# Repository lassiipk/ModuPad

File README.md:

# MODUPAD
| CAD | *IRL* |
|-----------|-----|
|  |  |

**MODUPAD** is a compact **3×3 programmable macropad with a rotary encoder** designed with a **macro‑first, learning‑driven philosophy**.  

This project represents a **from‑scratch learning journey** covering electronics, schematic design, PCB layout, firmware architecture, and documentation—while still resulting in a practical, daily‑use device.

---
<!--
## Device Identity

> **MODUPAD** is a **3×3 macropad + rotary encoder** with layered keymaps, encoder‑driven system control, and an event‑based OLED interface.

---

## Project Goals

- Learn electronics **from near zero** through hands‑on design
- Design a complete keyboard matrix with diodes
- Integrate a microcontroller, rotary encoder, and OLED display
- Build a full PCB in KiCad (schematic → layout → DRC‑clean)
- Design firmware architecture before hardware arrival
- Practice clean documentation and GitHub‑based version control
- Produce a focused, usable macropad without feature creep

This project prioritizes **learning clarity, reasoning, and correctness** over visual complexity.
-->

<!--
## Final Key Features (As Built)

- **3×3 key matrix (9 keys)** dedicated entirely to macros
- **Multiple firmware layers**
  - Layer 0 (Default)
  - Layer 1 (Fn layer)
  - Layer 2 (planned / future)
- **EC11 rotary encoder**
  - Rotation: system volume control
  - Button: OLED mode control
- **0.91” 128×32 I²C OLED**
  - Animation mode
  - Text mode
  - Status mode
  - Full OFF state
- **USB‑C connectivity**
- **Windows‑focused macro design** (Windows 10 & 11)
- **No RGB lighting** (removed during redesign to reduce complexity)

---
<!--
## Encoder Behavior

### Encoder Rotation
- Controls **system volume only**
- Small step size for precision
- Works across **Windows 10 & 11**

### Encoder Button
- **Press:** Cycle OLED animations
- **Fn + Press:** Cycle text/status modes
- **Fn + Hold (3s):** OLED ON / OFF toggle

---

## OLED System

### OLED Modes
1. **Animation Mode**
   - Plays one full animation per `animation_xx.py`
   - Firmware auto‑detects all animation files
   - No hard limit on number of animations
2. **Text Mode**
   - Displays:
     - Creator name
     - Date & time
3. **Status Mode**
   - Displays system states (e.g. mute status)
4. **OFF Mode**
   - OLED fully powered down (true blank state)

OLED behavior is **event‑driven**, not continuously animated.

---

 ## Development Status (Current)

- [x] Concept defined
- [x] Schematic completed
- [x] PCB layout completed
- [x] DRC‑clean board
- [x] Case designed
- [x] Firmware architecture finalized
- [x] Firmware written
- [x] Project uploaded to GitHub
- [ ] Hardware fabrication & assembly
- [ ] Flashing & physical testing
-->

## Firmware Overview

- **Firmware Framework:** KMK (Python‑based)

---

<!-- **Reason for KMK**
  - Python readability
  - Clear firmware structure
  - No dependency on VIA
  - Easier reasoning without hardware in hand

Firmware was designed **before physical assembly**, allowing logic review and iteration in advance.

---

## Why MODUPAD?

**MODUPAD** stands for:
- **MODU** — Modular, adaptable, intentional
- **PAD** — A focused input device

Every decision made in this project supports **clarity, control, and learning**.

---

-->

## Bill of Materials (BOM):
- **Microcontroller:** Seeed Studio XIAO RP2040
- **Keys:** 9 × MX‑style switches
- **Diodes:** 10 1N4148 Diodes (matrix isolation)
- **Encoder:** EC11 rotary encoder with push button
- **Display:** 0.91” I²C OLED (128×32)
- **Connectivity:** USB‑C
- **Case:** Custom‑designed in Fusion 360, 3D‑printed

---

| Schematic | PCB | Case |
|-----------|-----|------|
|  |  |  |

---

### Timeline

**Project Started:** 19th December, 2025 | 11:58 PM

**Project Ended:** 2nd January, 2026 | 7:58 PM

**Project Submited:** 2nd January, 2026 | 11:17 PM

**Project 99% Completed:** 12 Febuary | 1:00 PM

**Project 100% Completed:** N/a

---

## License

This project is open‑source and intended for **educational and personal use**.

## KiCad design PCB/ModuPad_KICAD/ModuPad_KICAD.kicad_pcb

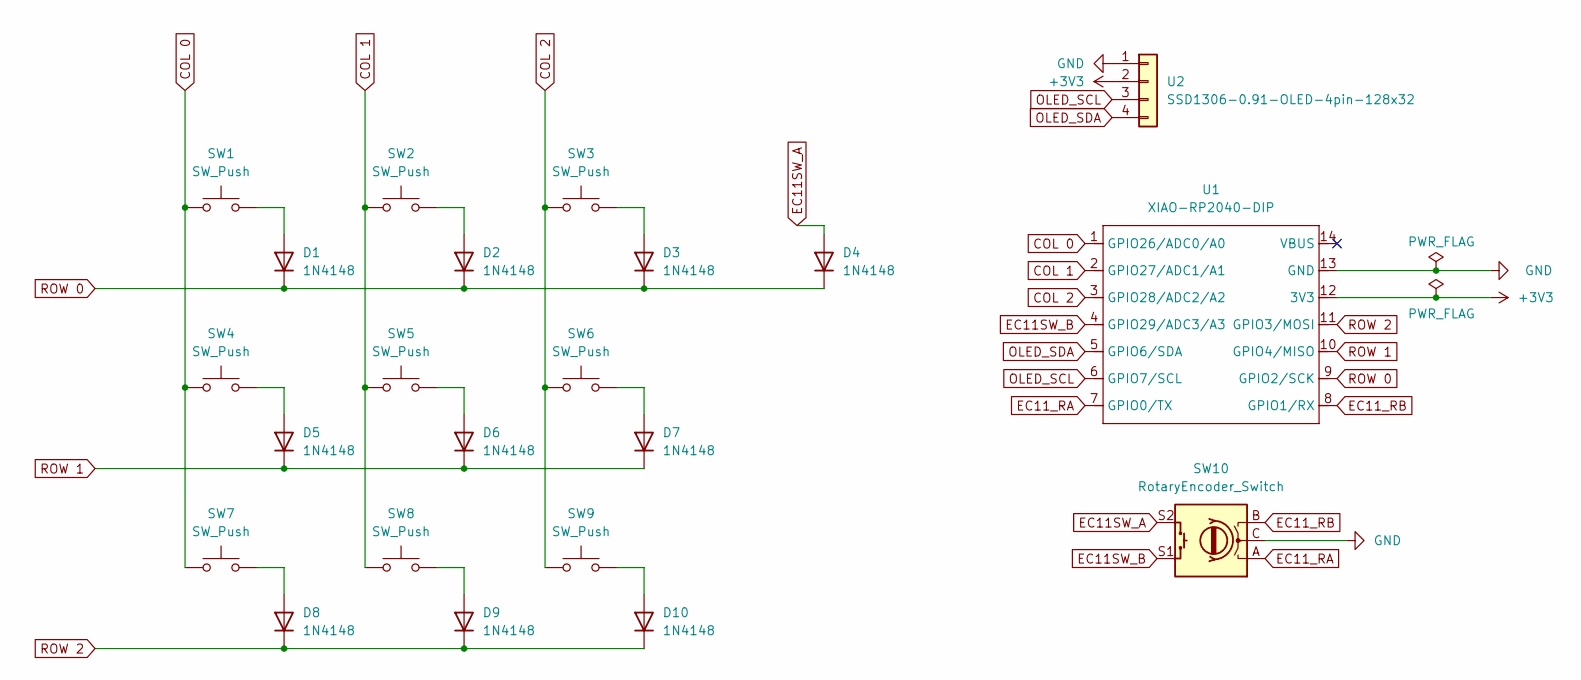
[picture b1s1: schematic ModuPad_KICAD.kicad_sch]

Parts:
D1, D2, D3, D4, D5, D6, D7, D8, D9, D10: 1N4148; D_DO-35_SOD27_P7.62mm_Horizontal
SW1, SW2, SW3, SW4, SW5, SW6, SW7, SW8, SW9: SW_Push; SW_Cherry_MX_1.00u_PCB
SW10: RotaryEncoder_Switch; RotaryEncoder_Alps_EC11E-Switch_Vertical_H20mm_CircularMoun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
U1: XIAO-RP2040-DIP
U2: SSD1306-0.91-OLED-4pin-128x32

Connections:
+3V3: U1.12 (3V3), U2.2
COL 0: SW1.1, SW4.1, SW7.1, U1.1 (GPIO26/ADC0/A0)
COL 1: SW2.1, SW5.1, SW8.1, U1.2 (GPIO27/ADC1/A1)
COL 2: SW3.1, SW6.1, SW9.1, U1.3 (GPIO28/ADC2/A2)
EC11SW_A: D4.2 (A), SW10.S2
EC11SW_B: SW10.S1, U1.4 (GPIO29/ADC3/A3)
EC11_RA: SW10.A, U1.7 (GPIO0/TX)
EC11_RB: SW10.B, U1.8 (GPIO1/RX)
GND: SW10.C, U1.13 (GND), U2.1
unnamed: D1.2 (A), SW1.2
unnamed: D2.2 (A), SW2.2
unnamed: D3.2 (A), SW3.2
unnamed: D5.2 (A), SW4.2
unnamed: D6.2 (A), SW5.2
unnamed: D7.2 (A), SW6.2
unnamed: D8.2 (A), SW7.2
unnamed: D9.2 (A), SW8.2
unnamed: D10.2 (A), SW9.2
OLED_SCL: U1.6 (GPIO7/SCL), U2.3
OLED_SDA: U1.5 (GPIO6/SDA), U2.4
ROW 0: D1.1 (K), D2.1 (K), D3.1 (K), D4.1 (K), U1.9 (GPIO2/SCK)
ROW 1: D5.1 (K), D6.1 (K), D7.1 (K), U1.10 (GPIO4/MISO)
ROW 2: D8.1 (K), D9.1 (K), D10.1 (K), U1.11 (GPIO3/MOSI)

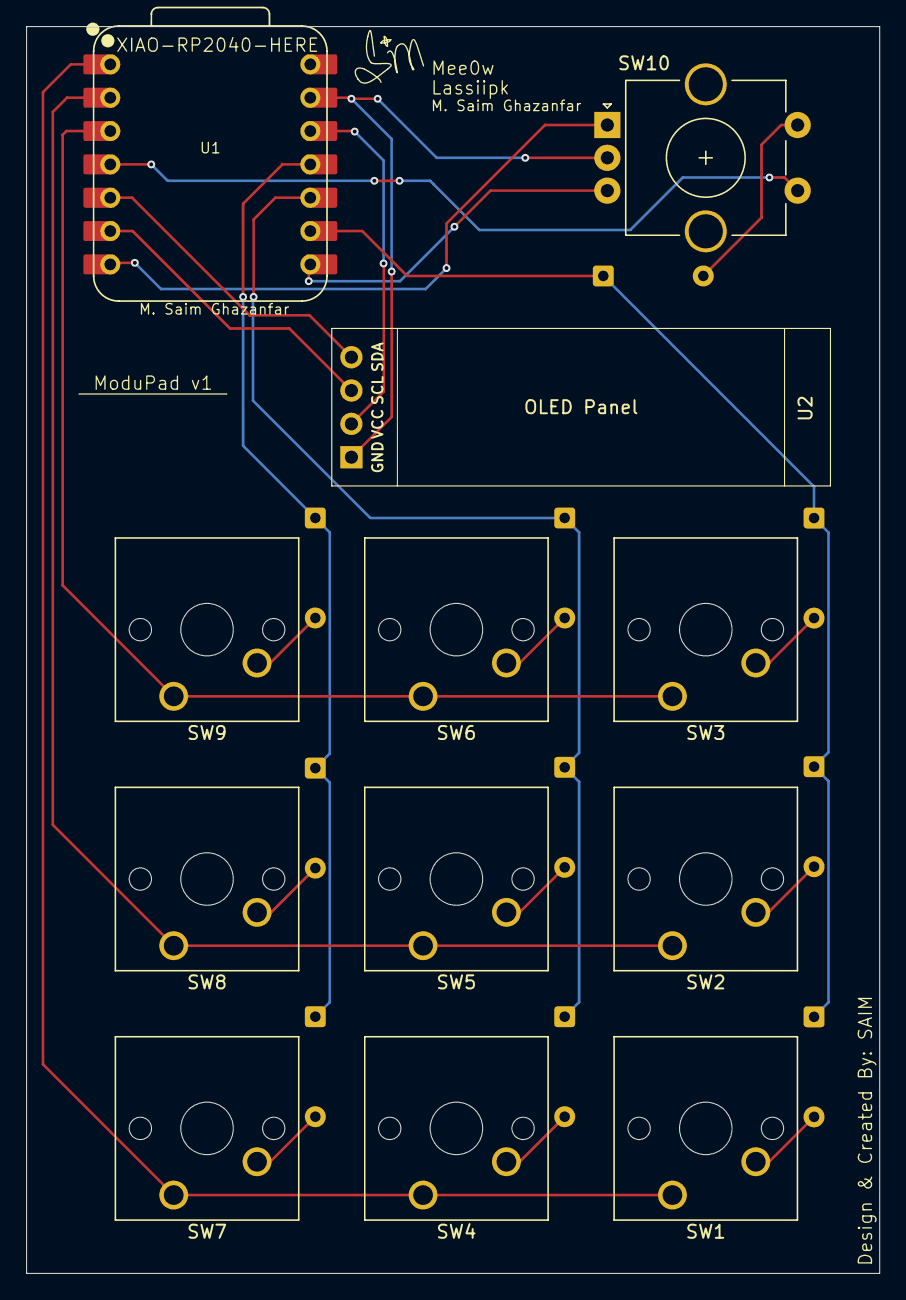
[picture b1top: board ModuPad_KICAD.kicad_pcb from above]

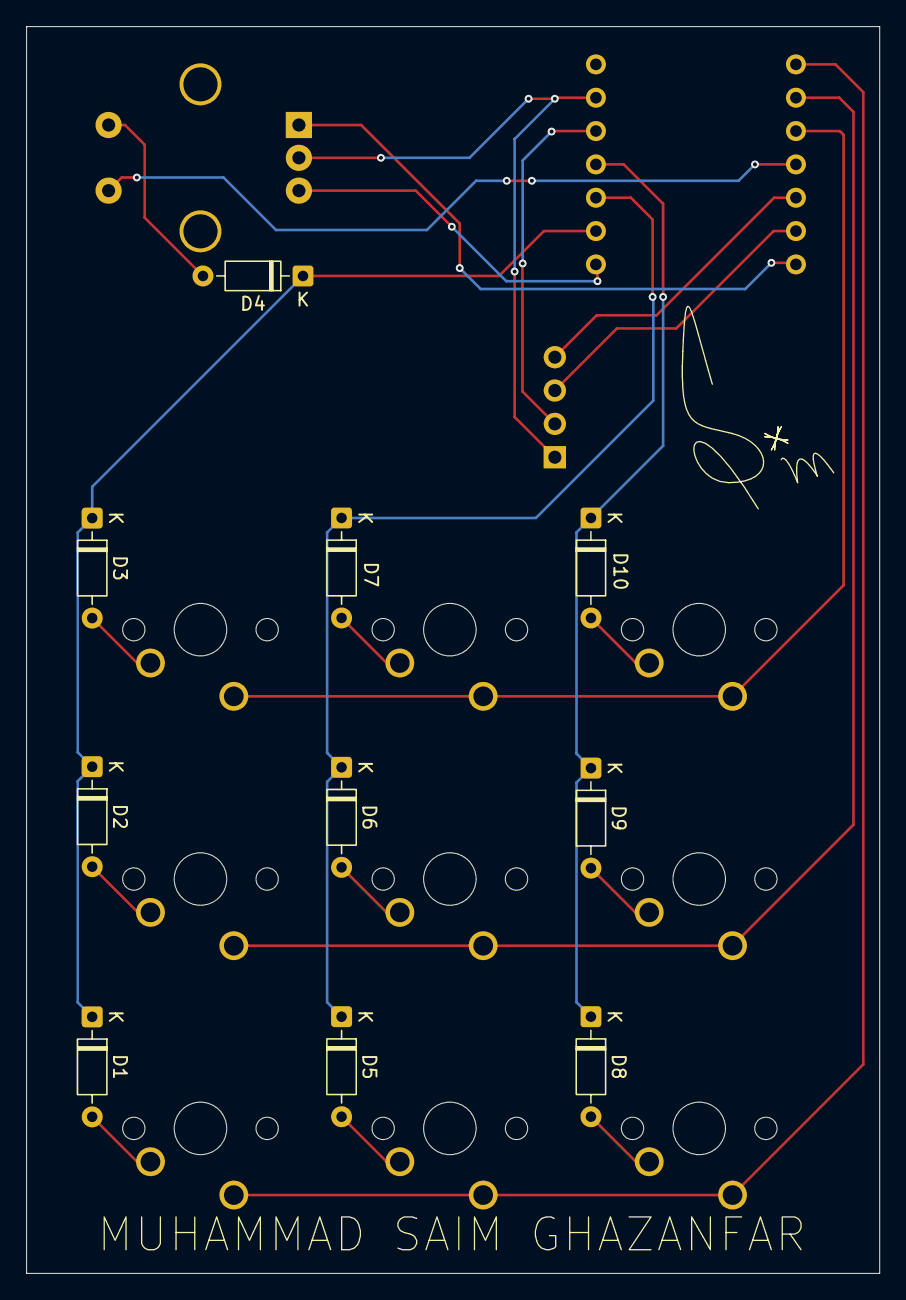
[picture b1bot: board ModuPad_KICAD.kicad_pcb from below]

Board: 2 copper layers, 65.0 x 95.0 mm, 22 parts (10 on the bottom side), 23 nets.

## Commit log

2026-01-02 ModuPad folder structure
2026-01-02 Removed Markdown files
2026-01-19 Rename ModuPad_Journal_02.md to ModuPad_Journal_02.md
2026-02-10 Add OLED-Testing.py for ModuPad display setup
2026-02-11 Update project timeline details in README
2026-02-11 Update project timeline with end and submission dates
2026-02-12 Implement macros and encoder functionality
    Added macro functionality for opening YouTube and Alt+Tabbing. Configured encoder handler and display settings.
2026-02-12 Refactor README with updated sections and tables
    Reorganized README structure and updated sections for clarity.
2026-02-17 Add project completion status to README
2026-02-23 Clean up README by removing commented content
    Removed commented sections about device identity, encoder behavior, and firmware reasoning from the README.
2026-02-23 Add project journal entries and images
    Documented the status of the soldering iron, PCB, and 3D-printed case orders. Added images related to the project.
2026-02-23 Add images to ModuPad Journal 02
    Added three images to the journal entry.
2026-02-23 ModuPad Journal 03
    Updated journal entry to reflect changes in firmware description and image link.
2026-02-23 Add firmware rewriting process
    Documented the process of rewriting firmware for the Seeed XIAO RP2040, including testing the encoder functionality and confirming no hardware issues.
2026-02-23 Shifted TO QMK
    Documented testing and implementation efforts for encoder and QMK firmware.
2026-02-23 Add ModuPad Journal 06 detailing case assembly issues
    Documented the delivery and assembly issues encountered with the ModuPad case, including measurement errors and necessary modifications.
2026-02-23 Key Testings
    Document progress on key switch testing and issues encountered.
2026-02-23 Add journal entry about OLED display troubleshooting
    Documented the troubleshooting process for OLED display issues and the resolution found by adding required libraries.
2026-02-23 Add timestamp to journal entry
    Added journal entry timestamp for clarity.
2026-02-23 Add image to ModuPad Journal entry
2026-02-23 Update ModuPad_Journal_05 with new entry
    Added a journal entry with an image of compiling status.
2026-02-23 Add image section and update journal content
    Added a section for images with three image entries and updated the existing content.
2026-02-23 Update ModuPad Journal 06 with images and notes
    Added images and additional content to ModuPad Journal 06.
2026-02-23 Add image to ModuPad Journal 07
2026-02-23 Updated README
    Added a Bill of Materials section to the README.
